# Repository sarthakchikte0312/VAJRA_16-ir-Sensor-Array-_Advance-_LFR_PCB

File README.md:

# VAJRA_16-ir-Sensor-Array-_Advance-_LFR_PCB
A 16 IR Sensor array for Fast Line Follower Bot, I have used the TCRT5000 Reflective Optical Sensor with Transistor Output which is connected to CD74HC4067 MUX 

## TCRT5000 Reflective Optical Sensor  

## Features
Package type: leaded  
Detector type: phototransistor     
Dimensions (L x W x H in mm): 10.2 x 5.8 x 7  
Peak operating distance: 2.5 mm  
Operating range within > 20 % relative collector current: 0.2 mm to 15 mm  
Typical output current under test: IC = 1 mA  
Daylight blocking filter  
Emitter wavelength: 950 nm

## Sensor Range

## Test circuit Digram

## CD74HCx4067 SOIC Topview 

## Features
Configuration	16:1  
Number of channels	1  
Power supply voltage - single (V)	1.8, 2.5, 3.3, 5  
Protocols	Analog  
Ron (typ) (Ω)	60  
CON (typ) (pF)	50  
ON-state leakage current (max) (µA)	8  
Bandwidth (MHz)	89  
Input/output continuous current (max) (A)	0.025  
Drain supply voltage (max) (V)	6  

## N20 Castor Ball 

# Features  
Overall diameter: ~22mm - 23.7mm  
Overall height: 15mm  
Large Ball Diameter: 12mm  
Mounting Hole Distance: 15mm

## VAJRA_Schematic

# PCB Layout

# VAJRA_3D_Front_view

# VAJRA_3D_Back_view

### BOM List
|S.No|Name|Quanity|
|---|---|---|
|1|TCRT5000|16|
|2|220 ohm SMD|16|
|3|10k ohm SMD|16|
|4|CD74HCx4067 16-Channel Analog Multiplexer|1|
|5|N-20 Castor Wheel|1|

will soon be Updating with my new design making it more reliable

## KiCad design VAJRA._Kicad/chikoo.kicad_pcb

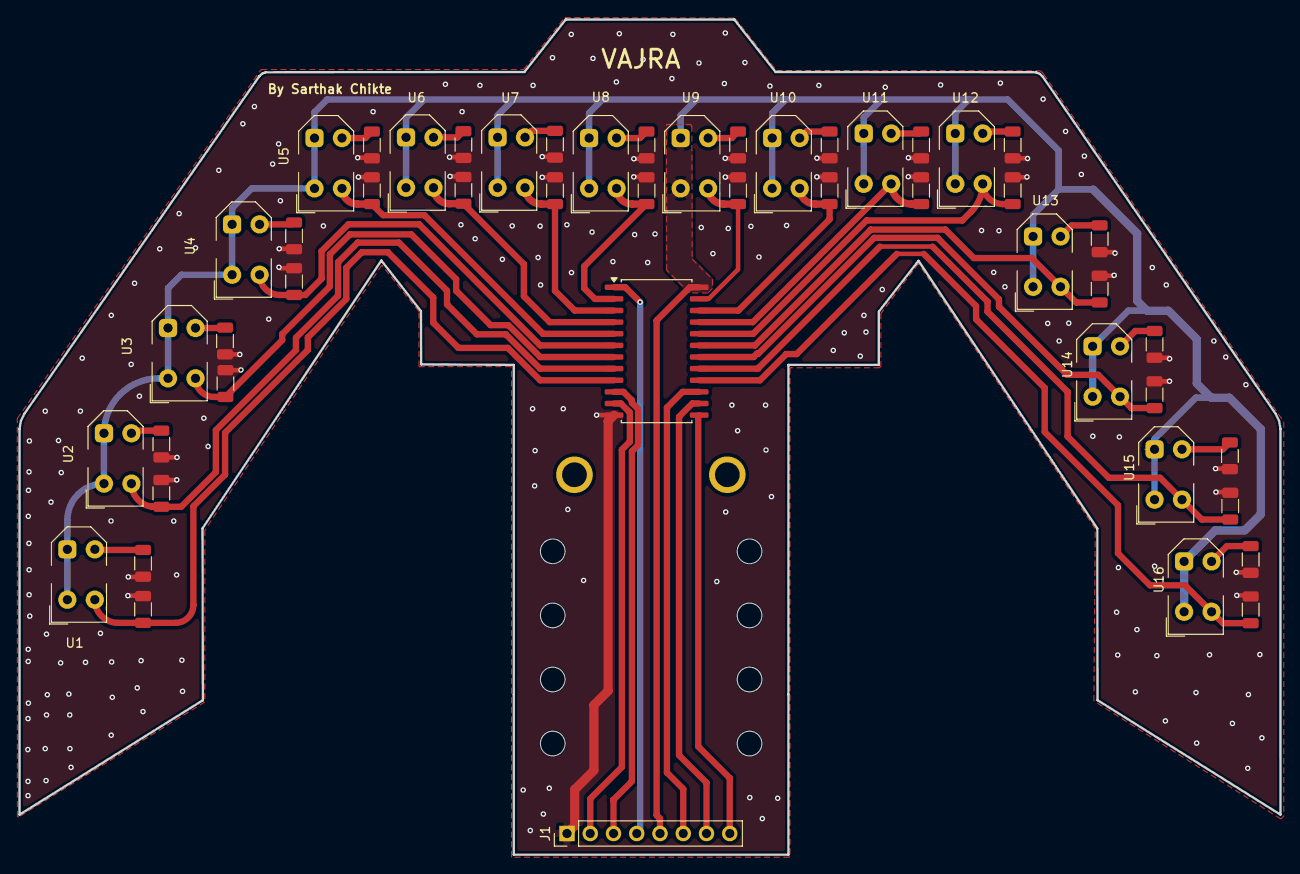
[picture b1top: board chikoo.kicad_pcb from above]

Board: 2 copper layers, 137.8 x 91.2 mm, 50 parts (0 on the bottom side), 40 nets.

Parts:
J1: Conn_01x08_Pin; PinHeader_1x08_P2.54mm_Vertical
R1, R3, R5, R7, R9, R11, R13, R15, R17, R19, R21, R23, R25, R27, R29, R31: 10k; R_1206_3216Metric
R2, R4, R6, R8, R10, R12, R14, R16, R18, R20, R22, R24, R26, R28, R30, R32: 220; R_1206_3216Metric
U1, U2, U3, U4, U5, U6, U7, U8, U9, U10, U11, U12, U13, U14, U15, U16: Vishay_TCRT5000
U17: CD74HC4067M; SOIC-24W_7.5x15.4mm_P1.27mm

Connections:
+5V: J1.5, U1.1 (A), U1.4 (C), U2.1 (A), U2.4 (C), U3.1 (A), U3.4 (C), U4.1 (A), U4.4 (C), U5.1 (A), U5.4 (C), U6.1 (A), U6.4 (C), U7.1 (A), U7.4 (C), U8.1 (A), U8.4 (C), U9.1 (A), U9.4 (C), U10.1 (A), U10.4 (C), U11.1 (A), U11.4 (C), U12.1 (A), U12.4 (C), U13.1 (A), U13.4 (C), U14.1 (A), U14.4 (C), U15.1 (A), U15.4 (C), U16.1 (A), U16.4 (C), U17.24 (VCC)
/COM: J1.4, U17.1 (COM)
/E: J1.6, U17.15 (~E)
/S0: J1.3, U17.10 (S0)
/S1: J1.2, U17.11 (S1)
/S2: J1.7, U17.14 (S2)
/S3: J1.8, U17.13 (S3)
GND: J1.1, R1.2, R2.1, R3.2, R4.1, R5.2, R6.1, R7.2, R8.1, R9.2, R10.1, R11.2, R12.1, R13.2, R14.1, R15.2, R16.1, R17.2, R18.1, R19.2, R20.1, R21.2, R22.1, R23.2, R24.1, R25.2, R26.1, R27.2, R28.1, R29.2, R30.1, R31.2, R32.1, U17.12 (GND)
unnamed: R2.2, U1.2 (K)
unnamed: R4.2, U2.2 (K)
unnamed: R6.2, U3.2 (K)
unnamed: R8.2, U4.2 (K)
unnamed: R10.2, U5.2 (K)
unnamed: R12.2, U6.2 (K)
unnamed: R14.2, U7.2 (K)
unnamed: R16.2, U8.2 (K)
unnamed: R18.2, U9.2 (K)
unnamed: R19.1, U10.3 (E), U17.22 (I9)
unnamed: R20.2, U10.2 (K)
unnamed: R21.1, U11.3 (E), U17.21 (I10)
unnamed: R22.2, U11.2 (K)
unnamed: R23.1, U12.3 (E), U17.20 (I11)
unnamed: R24.2, U12.2 (K)
unnamed: R25.1, U13.3 (E), U17.19 (I12)
unnamed: R26.2, U13.2 (K)
unnamed: R27.1, U14.3 (E), U17.18 (I13)
unnamed: R28.2, U14.2 (K)
unnamed: R29.1, U15.3 (E), U17.17 (I14)
unnamed: R30.2, U15.2 (K)
unnamed: R31.1, U16.3 (E), U17.16 (I15)
unnamed: R32.2, U16.2 (K)
unnamed: R1.1, U1.3 (E), U17.9 (I0)
unnamed: R3.1, U2.3 (E), U17.8 (I1)
unnamed: R5.1, U3.3 (E), U17.7 (I2)
unnamed: R7.1, U4.3 (E), U17.6 (I3)
unnamed: R9.1, U5.3 (E), U17.5 (I4)
unnamed: R11.1, U6.3 (E), U17.4 (I5)
unnamed: R13.1, U7.3 (E), U17.3 (I6)
unnamed: R15.1, U8.3 (E), U17.2 (I7)
unnamed: R17.1, U9.3 (E), U17.23 (I8)

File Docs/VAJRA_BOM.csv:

Reference,Qty,Value,DNP,Exclude from BOM,Exclude from Board,Footprint,Datasheet
J1,1,Conn_01x08_Pin,,,,Connector_PinHeader_2.54mm:PinHeader_1x08_P2.54mm_Vertical,
"R1,R3,R5,R7,R9,R11,R13,R15,R17,R19,R21,R23,R25,R27,R29,R31",16,10k,,,,Resistor_SMD:R_1206_3216Metric,
"R2,R4,R6,R8,R10,R12,R14,R16,R18,R20,R22,R24,R26,R28,R30,R32",16,220,,,,Resistor_SMD:R_1206_3216Metric,
"U1,U2,U3,U4,U5,U6,U7,U8,U9,U10,U11,U12,U13,U14,U15,U16",16,,,,,TCRT_sarth:Vishay_TCRT5000,
U17,1,CD74HC4067M,,,,Package_SO:SOIC-24W_7.5x15.4mm_P1.27mm,http://www.ti.com/lit/ds/symlink/cd74hc4067.pdf

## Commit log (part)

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2025-12-12 Add images for sensor range and test circuit diagram
2025-12-12 Enhance README with component details and images
    Added detailed specifications and images for various components including TCRT5000 sensor, CD74HC4067 multiplexer, N20 castor ball, and PCB layout.
2025-12-13 Rename schematic section to VAJRA_Schematic
2025-12-19 Add note on future design improvements
    Added note about upcoming design updates for reliability.
2026-01-06 Create asset
2026-01-06 Add assets folder for images
2026-01-06 Fix image links in README for better accessibility
    Updated image links in README to use raw URLs from assets.
2026-01-06 Fix image link in README for TCRT5000 sensor
    Updated image link for TCRT5000 sensor pin configuration.
2026-01-06 Fix image links in README for sensor range and diagrams
    Updated image links in the README to point to the assets directory for better organization.
